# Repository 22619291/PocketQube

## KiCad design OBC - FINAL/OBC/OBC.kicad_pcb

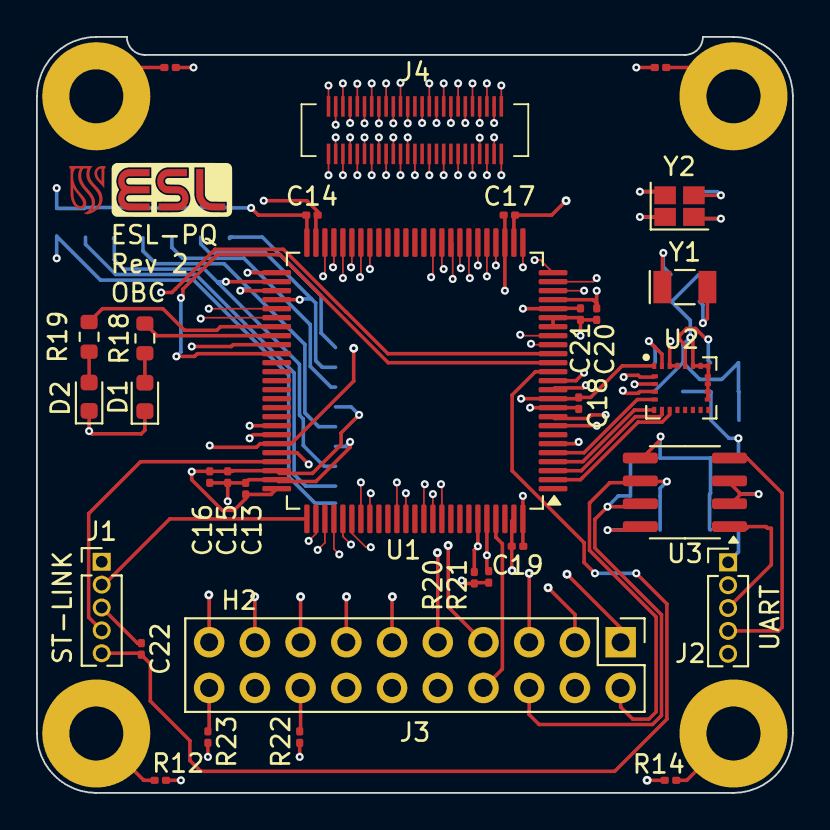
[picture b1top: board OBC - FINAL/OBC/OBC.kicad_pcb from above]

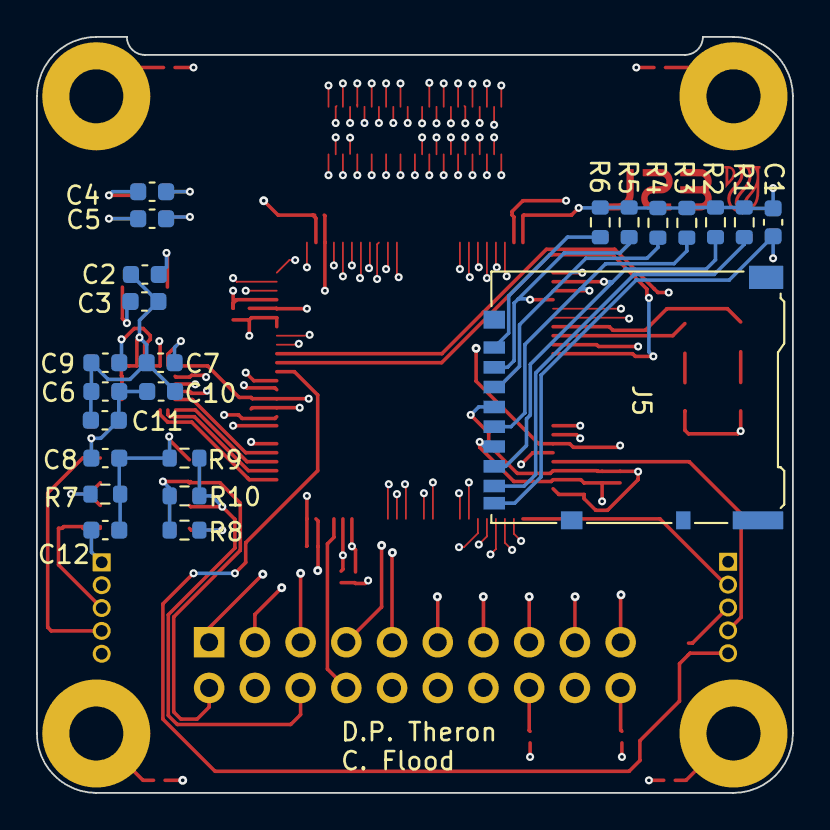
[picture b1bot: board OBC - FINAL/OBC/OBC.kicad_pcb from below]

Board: 4 copper layers, 42.0 x 42.0 mm, 58 parts (23 on the bottom side), 81 nets.

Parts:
C1, C8, C12: 10u; C_0603_1608Metric
C2, C3: 8p; C_0603_1608Metric
C4, C5: 12p; C_0603_1608Metric
C6, C7, C10, C11: 100n; C_0603_1608Metric
C9: 10n; C_0603_1608Metric
C13: 10u; C_0201_0603Metric
C14, C15, C16, C17, C18, C19, C22: 100n; C_0201_0603Metric
C20, C21: 1u; C_0201_0603Metric
D1, D2: LED; LED_0603_1608Metric
H1, H2, H3, H4: MountingHole_Pad; MountingHole_3mm_Pad
J1, J2: Conn_01x05; PinHeader_1x05_P1.27mm_Vertical
J3: ESL_PQ_MainHeader; ESL_PQ_Main_Header
J4: Conn_02x25_Odd_Even; HRS_DF40C-50DS-0.4V(51)
J5: Micro_SD_Card; microSD_HC_Hirose_DM3AT-SF-PEJM5
R1, R2, R3, R4, R5, R6, R7, R8, R9: 4k7; R_0603_1608Metric
R10: 120k; R_0603_1608Metric
R11, R12, R13, R14: 0; R_0201_0603Metric
R18, R19: 165; R_0603_1608Metric
R20, R21, R22, R23: 4k7; R_0201_0603Metric
U1: STM32L496VGTx; LQFP-100_14x14mm_P0.5mm
U2: LSM9DS1TR; LGA-24L_3x3.5mm_P0.43mm
U3: MAX485EDA; SOIC-8_3.9x4.9mm_P1.27mm
Y1: 32.768 kHz; Crystal_SMD_EuroQuartz_EQ161-2Pin_3.2x1.5mm
Y2: 16 MHz; Crystal_SMD_EuroQuartz_X22-4Pin_2.5x2.0mm

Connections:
3V3: J3.8, J4.14
5V: J3.3, J4.44
CSAG: U1.3 (PE4), U2.7 (CS_A/G)
CSM: U1.2 (PE3), U2.8 (CS_M)
DB1: J4.1, U1.78 (PC10)
DB2: J4.2, U1.77 (PA15)
DB3: J4.3, U1.83 (PD2)
DB4: J4.4, U1.82 (PD1)
DB5: J4.5, U1.48 (PB11)
DB7: J4.7, U1.86 (PD5)
DB8: J4.8, U1.81 (PD0)
DB9: J4.9, U1.47 (PB10)
DB11: J4.11, U1.87 (PD6)
DB12: J4.12, U1.80 (PC12)
DB13: J4.13, U1.46 (PE15)
DB15: J4.15, U1.89 (PB3)
DB16: J4.16, U1.79 (PC11)
DB17: J4.17, U1.45 (PE14)
DB19: J4.19, U1.90 (PB4)
DB20: J4.20, U1.55 (PD8)
DB21: J4.21, U1.44 (PE13)
DB23: J4.23, U1.91 (PB5)
DB24: J4.24, U1.56 (PD9)
DB25: J4.25, U1.43 (PE12)
DB28: J4.28, U1.24 (PA1)
DB29: J4.29, U1.36 (PB1)
DB30: J4.30, U1.17 (PC2)
DB32: J4.32, U1.23 (PA0)
DB33: J4.33, U1.35 (PB0)
DB34: J4.34, U1.18 (PC3)
DB37: J4.37, U1.34 (PC5)
DB38: J4.38, U1.25 (PA2)
DB41: J4.41, U1.33 (PC4)
DB42: J4.42, U1.26 (PA3)
DB45: J4.45, U1.32 (PA7)
DB46: J4.46, U1.29 (PA4)
DB49: J4.49, U1.31 (PA6)
DB50: J4.50, U1.30 (PA5)
DCap: C1.1, C6.2, C7.1, C8.1, C11.1, C12.1, C13.1, C14.1, C15.1, C16.1, C17.1, C18.1, C19.1, C20.1, C21.1, J1.1, J2.1, J3.6, J4.6, J5.4 (VDD), R1.1, R2.1, R3.1, R4.1, R5.1, R6.1, R8.1, R20.1, R21.1, R22.1, R23.2, U1.6 (VBAT), U1.11 (VDD), U1.21 (VREF+), U1.22 (VDDA), U1.28 (VDD), U1.50 (VDD), U1.73 (VDDUSB), U1.75 (VDD), U1.100 (VDD), U2.1 (VDDIO), U2.3 (VDDIO), U2.22 (VDD), U2.23 (VDD), U3.8 (VCC)
EPS-RST: J3.17, U1.97 (PE0)
GND: C1.2, C2.1, C3.1, C4.1, C5.1, C6.1, C7.2, C8.2, C9.1, C10.2, C11.2, C12.2, C13.2, C14.2, C15.2, C16.2, C17.2, C18.2, C19.2, C20.2, C21.2, C22.1, D1.1 (K), D2.1 (K), J1.3, J2.2, J3.2, J3.9, J3.12, J3.19, J4.18, J4.40, J5.6 (VSS), J5.9 (SHIELD), R7.2, R9.2, R11.1, R12.1, R13.1, R14.1, U1.10 (VSS), U1.19 (VSSA), U1.20 (VREF-), U1.27 (VSS), U1.49 (VSS), U1.74 (VSS), U1.99 (VSS), U2.14 (RES), U2.15 (RES), U2.16 (RES), U2.17 (RES), U2.18 (RES), U2.19 (GND), U2.20 (GND), U3.5 (GND), Y2.2, Y2.4
I2C-SCL: J3.11, R23.1, U1.15 (PC0), U1.60 (PD13)
I2C-SDA: J3.13, R22.2, U1.16 (PC1), U1.59 (PD12)
NRST: C22.2, J1.5, U1.14 (NRST)
unnamed: D1.2 (A), R18.1
unnamed: D2.2 (A), R19.1
unnamed: H1.1, R11.2
unnamed: H2.1, R12.2
unnamed: H3.1, R13.2
unnamed: H4.1, R14.2
unnamed: J5.8 (DAT1), R1.2
unnamed: J5.1 (DAT2), R6.2
unnamed: C10.1, U2.24 (C1)
unnamed: C9.2, U2.21 (CAP)
OSC32_IN: C2.2, U1.8 (PC14), Y1.1
OSC32_OUT: C3.2, U1.9 (PC15), Y1.2
OSC_IN: C4.2, U1.12 (PH0), Y2.1
OSC_OUT: C5.2, U1.13 (PH1), Y2.3
PPS: J3.14, J4.43, U1.70 (PA11)
PWR: R18.2, U1.58 (PD11)
RS-A: J3.20, R8.2, R10.1, U3.6 (A)
RS-B: J3.18, R9.1, R10.2, U3.7 (B)
RS-EN: R7.1, U1.71 (PA12), U3.2 (~RE), U3.3 (DE)
S1_5V: J3.5, J4.47
S2_3V3: J3.7, J4.10
S2_5V: J3.4, J4.48
SAOG: U1.5 (PE6), U2.5 (SDO_A/G)
SAOM: U1.4 (PE5), U2.6 (SDO_M)
SCL: R20.2, U1.95 (PB8), U2.2 (SCL/SPC)
SDA: R21.2, U1.96 (PB9), U2.4 (SDA/SDI/SDO)
SPI MISO: J5.7 (DAT0), R2.2, U1.52 (PB13)
SPI MOSI: J5.3 (CMD), R4.2, U1.51 (PB12)
SPI NSS: J5.2 (DAT3/CD), R5.2, U1.54 (PB15)
SPI SCK: J5.5 (CLK), R3.2, U1.53 (PB14)
SWCLK: J1.2, U1.76 (PA14)
SWDIO: J1.4, U1.72 (PA13)
TX: R19.2, U1.57 (PD10)
USART RX: J2.4, U1.69 (PA10), U3.4 (DI)
USART TX: J2.3, U1.68 (PA9), U3.1 (RO)
Unreg Bat: J3.10, J4.22
Unreg Solar: J3.1, J4.36

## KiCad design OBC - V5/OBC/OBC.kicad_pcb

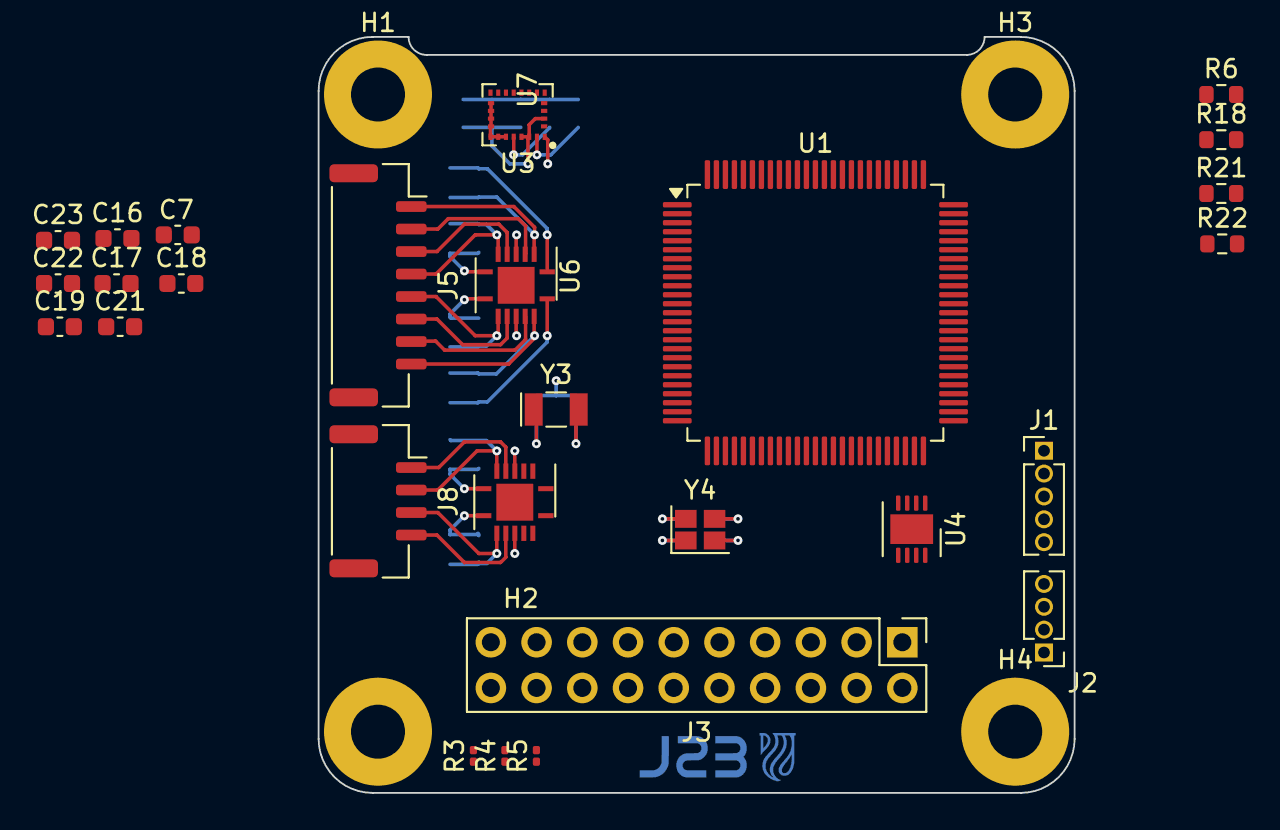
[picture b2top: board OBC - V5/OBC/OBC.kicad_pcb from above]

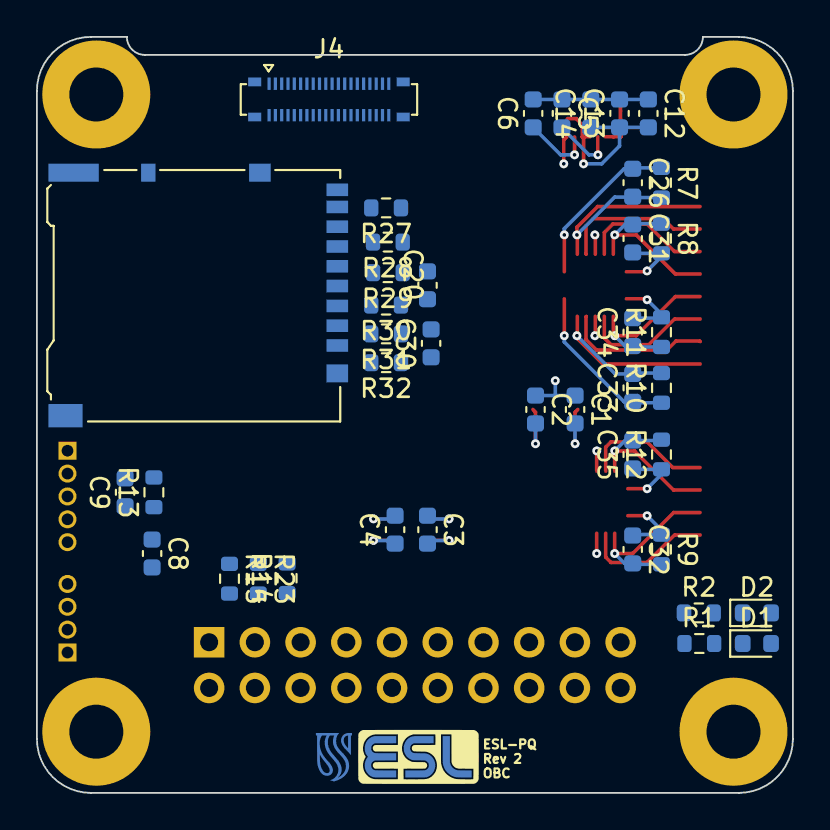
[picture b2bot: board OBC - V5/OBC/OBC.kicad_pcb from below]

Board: 4 copper layers, 42.0 x 42.0 mm, 72 parts (41 on the bottom side), 58 nets.

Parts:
C1, C2: 8p; C_0603_1608Metric
C3, C4: 12p; C_0603_1608Metric
C5: 10n; C_0603_1608Metric
C6, C7, C8, C12, C13, C17, C18, C19, C20, C21, C22, C23: 100n; C_0603_1608Metric
C9, C14, C16, C30: 10u; C_0603_1608Metric
C26, C31, C32, C33, C34, C35: 220p; C_0603_1608Metric
D1, D2: LED; LED_0603_1608Metric
H1, H2, H3, H4: MountingHole_Pad; MountingHole_3mm_Pad
J1: Conn_01x05; PinHeader_1x05_P1.27mm_Vertical
J2: Conn_01x04; PinHeader_1x04_P1.27mm_Vertical
J3: ESL_PQ_MainHeader; ESL_PQ_Main_Header
J4: Conn_02x20_Odd_Even; Hirose_BM24_BM24-40DP-2-0.35V_2x20_P0.35mm_PowerPin2_Vertic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
J5: Conn_01x08_MountingPin; JST_GH_SM08B-GHS-TB_1x08-1MP_P1.25mm_Horizontal
J6: Micro_SD_Card; microSD_HC_Hirose_DM3AT-SF-PEJM5
J8: Conn_01x04_MountingPin; JST_GH_SM04B-GHS-TB_1x04-1MP_P1.25mm_Horizontal
R1, R2: 165; R_0603_1608Metric
R3, R4, R5: 0; R_0201_0603Metric
R6, R18, R21, R22: 0; R_0603_1608Metric
R7, R8, R9, R10, R11, R12: 470; R_0603_1608Metric
R13, R14, R15, R27, R28, R29, R30, R31, R32: 4k7; R_0603_1608Metric
R23: 120k; R_0603_1608Metric
U1: STM32L496VGTxP; LQFP-100_14x14mm_P0.5mm
U3: LSM9DS1TR; LGA-24L_3x3.5mm_P0.43mm
U4: LTC2850HDD#PBF; DFN-8-1EP_3x3mm_P0.5mm_EP1.65x2.38mm
U6, U7: OPA4330; Texas_S-PVQFN-N14
Y3: 32.768 kHz; Crystal_SMD_EuroQuartz_EQ161-2Pin_3.2x1.5mm
Y4: 80 MHz; Crystal_SMD_EuroQuartz_X22-4Pin_2.5x2.0mm

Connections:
1+: J5.2, U6.3 (+INA)
1-: C26.2, J5.1, R7.2, U6.2 (-INA)
2+: J5.3, U6.5 (+INB)
2-: C31.1, J5.4, R8.1, U6.6 (-INB)
3+: J5.6, U6.10 (+INC)
3-: C34.1, J5.5, R11.1, U6.9 (-INC)
3V3: J3.8, R3.1
4+: J5.7, U6.12 (+IND)
4-: C33.2, J5.8, R10.2, U6.13 (-IND)
5+: J8.4, U7.10 (+INC)
5-: C32.2, J8.3, R9.2, U7.9 (-INC)
6+: J8.1, U7.5 (+INB)
6-: C35.2, J8.2, R12.2, U7.6 (-INB)
CSAG: U1.15 (PC0), U3.7 (CS_A/G)
CSM: U1.17 (PC2), U3.8 (CS_M)
DCap: C8.1, C9.1, C12.2, C13.1, C14.1, C16.1, C17.1, C18.1, C19.1, C20.1, C21.1, C22.1, C23.1, C30.1, J1.1, J2.1, J6.4 (VDD), R3.2, R4.1, R5.2, R14.1, R27.1, R28.1, R29.1, R30.1, R31.1, R32.1, U1.6 (VBAT), U1.11 (VDD), U1.22 (VDDA), U1.28 (VDD), U1.48 (VDD12), U1.50 (VDD), U1.73 (VDDUSB), U1.75 (VDD), U1.98 (VDD12), U1.100 (VDD), U3.1 (VDDIO), U3.3 (VDDIO), U3.22 (VDD), U3.23 (VDD), U4.8 (VCC), U6.4 (V+), U7.4 (V+)
GND: C1.1, C2.1, C3.1, C4.1, C5.1, C6.2, C7.2, C8.2, C9.2, C12.1, C13.2, C14.2, C16.2, C17.2, C18.2, C19.2, C20.2, C21.2, C22.2, C23.2, C30.2, D1.1 (K), D2.1 (K), J1.3, J2.2, J3.2, J3.9, J3.12, J3.19, J6.6 (VSS), J6.9 (SHIELD), R6.1, R13.2, R15.2, R18.1, R21.1, R22.1, U1.10 (VSS), U1.19 (VSSA), U1.27 (VSS), U1.49 (VSS), U1.74 (VSS), U1.99 (VSS), U3.14 (RES), U3.15 (RES), U3.16 (RES), U3.17 (RES), U3.18 (RES), U3.19 (GND), U3.20 (GND), U4.5 (GND), U6.11 (V-), U6.15 (PAD), U7.11 (V-), U7.15 (PAD), Y4.2, Y4.4
I2C-SCL: J3.11, U1.92 (PB6)
I2C-SDA: J3.13, U1.93 (PB7)
NRST: C7.1, J1.5, U1.14 (NRST)
unnamed: D1.2 (A), R1.1
unnamed: D2.2 (A), R2.1
unnamed: H1.1, R6.2
unnamed: H2.1, R18.2
unnamed: H3.1, R21.2
unnamed: H4.1, R22.2
unnamed: J6.8 (DAT1), R27.2
unnamed: J6.1 (DAT2), R32.2
unnamed: C6.1, U3.24 (C1)
unnamed: C5.2, U3.21 (CAP)
OPA1: C26.1, R7.1, U1.23 (PA0), U6.1 (OA)
OPA2: C31.2, R8.2, U1.24 (PA1), U6.7 (OB)
OPA3: C34.2, R11.2, U1.25 (PA2), U6.8 (OC)
OPA4: C33.1, R10.1, U1.26 (PA3), U6.14 (OD)
OPA5: C32.1, R9.1, U1.29 (PA4), U7.8 (OC)
OPA6: C35.1, R12.1, U1.30 (PA5), U7.7 (OB)
OSC32_IN: C1.2, U1.8 (PC14), Y3.1
OSC32_OUT: C2.2, U1.9 (PC15), Y3.2
OSC_IN: C3.2, U1.12 (PH0), Y4.1
OSC_OUT: C4.2, U1.13 (PH1), Y4.3
PPS: J3.14, U1.91 (PB5)
RS-A: J3.20, R14.2, R23.1, U4.6 (A)
RS-B: J3.18, R15.1, R23.2, U4.7 (B)
RS-EN: R13.1, U1.35 (PB0), U4.2 (~RE), U4.3 (DE)
S1_3V3: J3.6, R4.2
S2_3V3: J3.7, R5.1
SAOG: U1.16 (PC1), U3.5 (SDO_A/G)
SAOM: U1.18 (PC3), U3.6 (SDO_M)
SCL: U1.52 (PB13), U3.2 (SCL/SPC)
SDA: U1.53 (PB14), U3.4 (SDA/SDI/SDO)
SPI MISO: J6.7 (DAT0), R28.2, U1.45 (PE14)
SPI MOSI: J6.3 (CMD), R30.2, U1.46 (PE15)
SPI NSS: J6.2 (DAT3/CD), R31.2, U1.43 (PE12)
SPI SCK: J6.5 (CLK), R29.2, U1.44 (PE13)
SWCLK: J1.2, U1.76 (PA14)
SWDIO: J1.4, U1.72 (PA13)
USART RX: J2.4, U1.34 (PC5), U4.4 (DI)
USART TX: J2.3, U1.33 (PC4), U4.1 (RO)

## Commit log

2024-04-18 NIEL OBC 1
2024-04-18 added mcu
2024-04-22 Niel 2
2024-04-25 Schematic Finished
2024-05-10 Niel V3
2024-05-10 64 pin labels in new 64 pin file
2024-06-04 PQ V12
2024-06-04 FINAL
2024-06-04 Final 1
2024-06-10 OBC - Final 2
